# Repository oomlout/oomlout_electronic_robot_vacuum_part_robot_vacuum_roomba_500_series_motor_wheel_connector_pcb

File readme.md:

# Oomlout Electronic Robot Vacuum Part Robot Vacuum Roomba 500 Series Motor Wheel Connector Pcb

Oomlout Electronic Robot Vacuum Part Robot Vacuum Roomba 500 Series Motor Wheel Connector Pcb  

## corel working

## oolc_production
Laser cutting production files can be found in the [oolc_production](oolc_production) folder.

## 3d printing files
3d printing files can be found in the [scad_output](scad_output) folder.

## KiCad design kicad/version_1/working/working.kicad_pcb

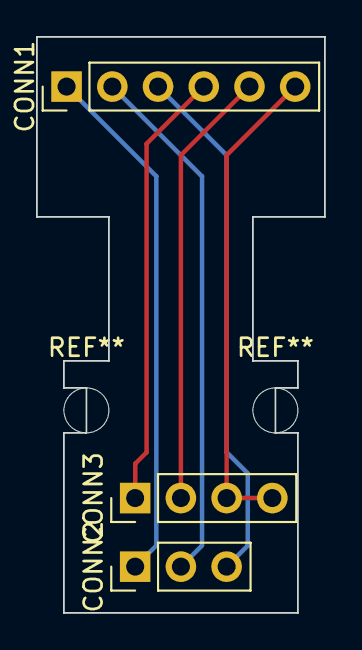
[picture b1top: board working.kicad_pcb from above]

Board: 2 copper layers, 16.0 x 32.0 mm, 3 parts (0 on the bottom side), 6 nets.

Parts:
CONN1: hi16pth_electronic_header_2_54_mm_6_pin_through_h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; hi16pth_electronic_header_2_54_mm_6_pin_through_hole
CONN2: hi13pth_electronic_header_2_54_mm_3_pin_through_h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; hi13pth_electronic_header_2_54_mm_3_pin_through_hole
CONN3: hi14pth_electronic_header_2_54_mm_4_pin_through_h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; hi14pth_electronic_header_2_54_mm_4_pin_through_hole

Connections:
5v: CONN1.3, CONN2.3
a: CONN1.1, CONN2.1
b: CONN1.2, CONN2.2
enc: CONN1.4, CONN3.1
gnd: CONN1.6, CONN3.3, CONN3.4
switch_a: CONN1.5, CONN3.2

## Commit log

2024-11-24 initial
2024-11-24 produciton files
2024-11-25 comitting after processing for oolc
2024-11-25 commiting after auto generation
2024-12-10 version 2
